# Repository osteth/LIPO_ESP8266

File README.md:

# LIPO ESP8266

The LIPO Esp8266 is a lipo battery recharge circuit and an ESP8266 wifi module that can be used to creating IOT projects such as mobile web servers, wifi repeaters, etc.

This board is based on the sparkfun LIPO charger basic, incorperates an ESP8266-12 module and is designed to use the 2000mAh Lithium Ion Polymer Battery from sparkfun.

SparkFun LiPo Charger Basic - Mini-USB - https://www.sparkfun.com/products/10401

Lithium Ion Polymer Battery - 2000mAh- https://www.sparkfun.com/products/8483

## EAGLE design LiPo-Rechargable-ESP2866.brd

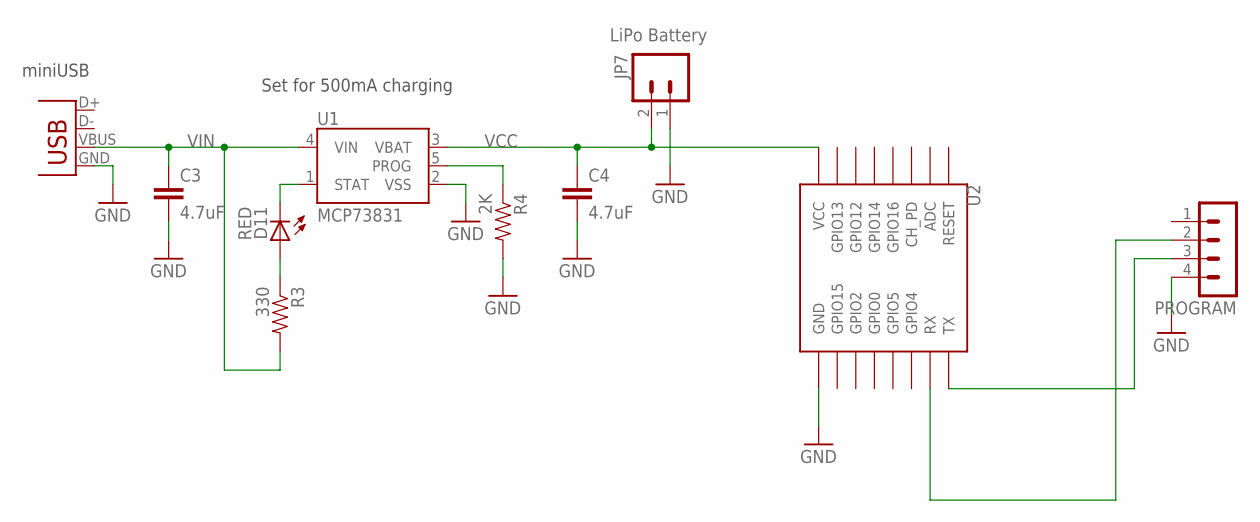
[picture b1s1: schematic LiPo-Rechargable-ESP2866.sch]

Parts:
C3, C4: 4.7uF; 0402-CAP
D11: RED; LED-0603
JP7: LiPo Battery; JST-2-SMD
PROGRAM: MA04-1
R3: 330; 0402-RES
R4: 2K; 0402-RES
U1: MCP73831; SOT23-5
U2: ESP12
X1: Micro USB; USB-MINIB

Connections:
GND: C3.2, C4.2, JP7.1, PROGRAM.4, R4.2, U1.2 (VSS), U2.GND, X1.GND
unnamed: PROGRAM.2, U2.RX
unnamed: PROGRAM.3, U2.TX
unnamed: D11.A, R3.1
PROG: R4.1, U1.5 (PROG)
STAT: D11.C, U1.1 (STAT)
VCC: C4.1, JP7.2, U1.3 (VBAT), U2.VCC
VIN: C3.1, R3.2, U1.4 (VIN), X1.VBUS

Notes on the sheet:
Set for 500mA charging
miniUSB

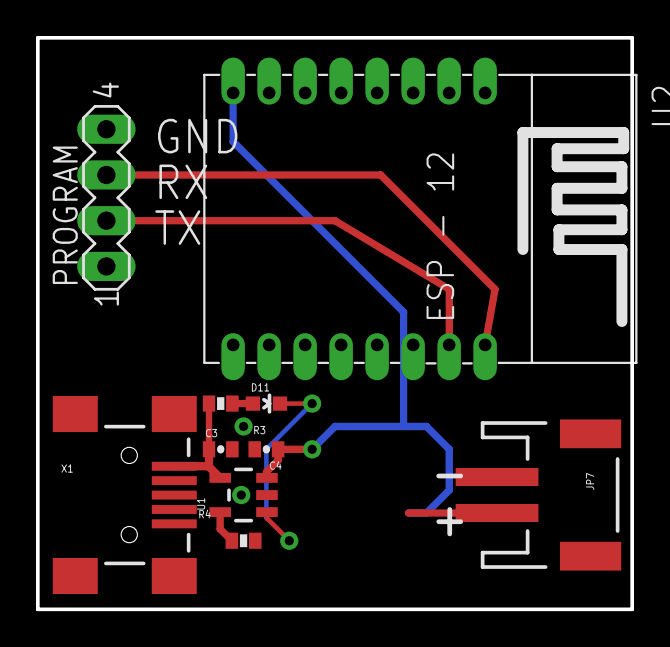
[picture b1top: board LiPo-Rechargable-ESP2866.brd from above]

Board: 2 copper layers, 33.0 x 31.8 mm, 10 parts (0 on the bottom side), 8 nets.

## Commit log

2016-04-30 :circus_tent: Added .gitattributes & .gitignore files
2016-04-30 Add resources
2016-04-30 adding pictures
2016-04-30 again
2016-04-30 make pictures work
2016-04-30 daefsrtghj
